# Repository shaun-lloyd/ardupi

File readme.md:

# ArduPi, Ardupilot + Raspberry Pi

ArduPi is an Raspberry Pi hat with sensors and drivers to run ardupilot.

Based entirely on work and with the guidance and lead of [Muhammad Hefny, OBAL](https://github.com/HefnySco/OBAL "Muhammad Hefny, OBAL").

## Thanks

This project stands on the ardupilot & raspberry pi platforms, ardupilot in particular is an outstanding example of open source communities flourishing.

[OBAL, Mohammad Hefny](https://github.com/HefnySco/OBAL "OBAL, Mohammad Hefny"). ArduPi has been created using [OBAL](https://github.com/HefnySco/OBAL "OBAL") as a reference and design inspiration.

ArduPi-v0.1 == OBAL

## Development

Everything in the entire toolchain must be free software. No dependancy on any non-free software is acceptable. With exception of ardupilot:matlab. "I would really love to hear from anyone that can suggest or give advise on how to or the process involved in porting the current control theory to a free software platform, potential financial support is available to any project that can resonable accomplish this task".

The board itself is developed using Kicad v6.0 on both ubuntu and windows.

Linux is the focus however Kicad is available on mac & windows so there is no reason developement couldn't be done any OS and indeed is. As long as anything done on windows is "do-able" on linux then that's cool.

## Solution: ArduPi
The Raspberry pi platform requires some additional hardware to be able to control a vehicle.
The RPI handles ardupilot-cpu / comms:control-telemetry-video, and ardupi handles everything else.

This hardware is designed using OBAL reference.

### Hardware Specification

Raspberry Pi 4b hat.

### IC
- ULN2803:led,buzzer
- ADS1115:current voltage sensor
- IMU9650:IMU
- BMP280:Barometer

### Module
- GPS:ublox module
- ExpressLRS

### Connections
- ?6S 25V input. Bypass circuit for driving motors and BEC with ?5v@6a
- +5V@3A input
- PWM:pca9685
- ESC
- UART
- I2C
- SPI
- Serial
- PWM:servo/esc
- RC:Rx
- Buzzer & Safety Circuit

### Software
TODO

## How you can help :)

Any and all feedback is encouraged.

Anyone with electronics experience can look over our shematics and crtique or even better suggest better circuits or components.

1. QA our schematics/pcb layout.

2. I would like to include ADSB,optical flow,lidar & airspeed sensor. So anyone with expertise and some spare time willing to
share would be really appreciated.

Help documenting and organise schematics such that new users in particular can easily understand and fork.

Suggest better IC's, sensors and features.

Thanks.

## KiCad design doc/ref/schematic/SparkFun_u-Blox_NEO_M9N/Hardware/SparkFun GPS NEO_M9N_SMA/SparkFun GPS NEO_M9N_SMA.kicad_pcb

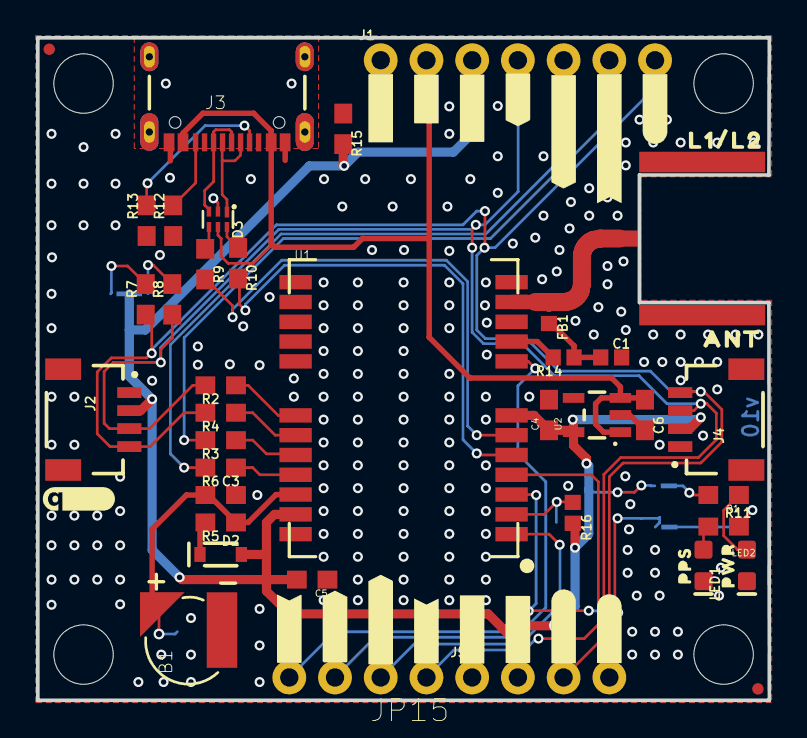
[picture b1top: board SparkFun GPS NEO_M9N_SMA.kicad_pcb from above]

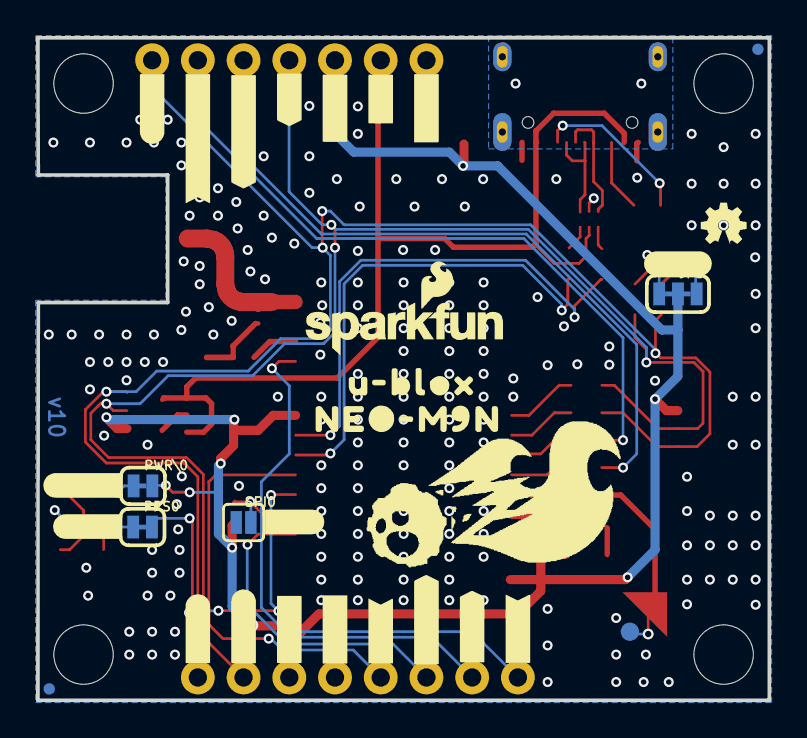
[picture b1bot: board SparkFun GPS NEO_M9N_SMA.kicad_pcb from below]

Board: 2 copper layers, 40.6 x 36.8 mm, 94 parts (31 on the bottom side), 36 nets.

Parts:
B1: 6.8MM_COIN_CELL; ML414H_IV01E
C1: 47pF; 0402
C3, C4, C6: 1.0uF; 0603
C5: 0.1uF; 0603
D2: 0.5A/40V/420mV; SOD-323
D3: PRTR5V0U2F; SOT886
E1: ANTENNA-GROUNDEDEDGE_SMA_SMD; SMA-EDGE-SMD
FB1: FERRITE_BEAD-120_OHM-0402; 0402
FRAME1: FRAME-LETTER; CREATIVE_COMMONS
J1: 1X07_NO_SILK
J2, J4: Qwiic Right Angle; JST04_1MM_RA
J3: USB-C-16P-2LAYER-PADS
J5: 1X04_NO_SILK
JP1, JP31, JP91, JP101: STAND-OFF
JP5: JUMPER-SMT_3_2-NC_TRACE_SILK; SMT-JUMPER_3_2-NC_TRACE_SILK
JP15: 1X04_NO_SILK
JP21, JP61, JP71, JP81: FIDUCIALUFIDUCIAL; MICRO-FIDUCIAL
LED1: BLUE; LED-0603
LED2: RED; LED-0603
LOGO1: OSHW-LOGOMINI; OSHW-LOGO-MINI
LOGO2: SFE_LOGO_NAME_FLAME.1_INCH; SFE_LOGO_NAME_FLAME_.1
PPS0: JUMPER-SMT_2_NC_TRACE_SILK; SMT-JUMPER_2_NC_TRACE_SILK
PWR\0: JUMPER-SMT_2_NC_TRACE_SILK; SMT-JUMPER_2_NC_TRACE_SILK
R1, R5, R11: 1k; 0603
R2, R3, R4, R6: 33; 0603
R7, R8: 2.2k; 0603
R9, R10: 27; 0603
R12, R13: 5.1k; 0603
R14: 33; 0402
R15: 100k; 0603
R16: 10k; 0402
SPI0: JUMPER-SMT_2_NO_SILK; SMT-JUMPER_2_NO_SILK
TP1: TEST-POINT3X4; PAD.03X.04
U1: U-BLOX_NEO-M9N; NEO-M9N_M8T_M8U
U2: 3.3V; SOT23-5
U$1: ##CS##9
U$2: U#BLOX19
U$3: ##SAFE##15
U$4, U$5, U$39, U$40: #3V3#6
U$6, U$42: #5V#1
U$7, U$8, U$38, U$41: #GND#0
U$9: #INT#16
U$10: PPS7
U$11, U$32: #PPS#13
U$12: #SPI#22
U$13: PWR6
U$14: QWIIC_4MM
U$15: #RX#SDI#10
U$16: #SCK#12
U$17: #PWR#1
U$18: #SCL#18
U$19: #SDA#17
U$20: #TX#SDO#11
U$21: NEO_GPS_BOARD_SILK_FINAL#03#JPG
U$22: ##SAFE##11
U$23: L1#L28
U$24: ANT8
U$25: NEO#M9N20
U$26: ##CS##6
U$27: ##RST##12
U$28: ##RST##2
U$29: #I2C#3
U$30: #INT#10
U$31: #PPS#0
U$33: #RX#SDI#4
U$34: #SCK#3
U$35: #SCL#8
U$36: #SDA#9
U$37: #TX#SDO#5

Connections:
3.3V: C4.1, C5.2, D2.A, J1.3, J2.2, J4.2, J5.2, JP5.2, PWR\0.2, R15.2, R16.2, U1.7, U1.23, U2.5
5V: C6.1, D3.5, J1.2, J3.VBUS1, J3.VBUS2, U2.1, U2.3
D+: D3.4, R9.1
D-: D3.6, R10.1
D_SEL: R16.1, SPI0.2, U1.2
GND: B1.-, C1.2, C3.2, C4.2, C5.1, C6.2, D3.2, E1.GND@0, E1.GND@1, J1.1, J2.1, J3.GND, J3.GND2, J4.1, J5.1, LED1.C, LED2.C, R12.1, R13.1, R15.1, SPI0.1, U1.10, U1.12, U1.13, U1.24, U2.2
GPS_ANT1: E1.SIG, FB1.1, U1.11
INT: JP15.1, U1.4
unnamed: PWR\0.1, R1.2
unnamed: LED1.A, R11.1
unnamed: C1.1, FB1.2, R14.1
unnamed: PPS0.1, R11.2
unnamed: JP5.1, R8.2
unnamed: D2.C, R5.2
unnamed: J3.B5, R12.2
unnamed: JP5.3, R7.2
unnamed: J3.A5, R13.2
unnamed: LED2.A, R1.1
unnamed: R9.2, U1.6
unnamed: R10.2, U1.5
PPS: JP15.4, PPS0.2, U1.3
RXI/SDI: J1.5, R6.2
RXLV: R6.1, U1.21
SCL/SCK: J1.7, J2.4, J4.4, J5.4, R4.2, R7.1
SCL_LV: R4.1, U1.19
SDA/~CS: J1.4, J2.3, J4.3, J5.3, R2.2, R8.1
SDA_LV: R2.1, U1.18
SHLD: J3.SHLD1, J3.SHLD2, J3.SHLD3, J3.SHLD4
TXLV: R3.1, U1.20
TXO/SDO: J1.6, R3.2
USB_D+: D3.3, J3.A6, J3.B6
USB_D-: D3.1, J3.A7, J3.B7
VCC_RF: R14.2, U1.9
V_BATT: B1.+, C3.1, R5.1, TP1.P$1, U1.22
~RESET: JP15.3, U1.8
~SAFE: JP15.2, U1.1

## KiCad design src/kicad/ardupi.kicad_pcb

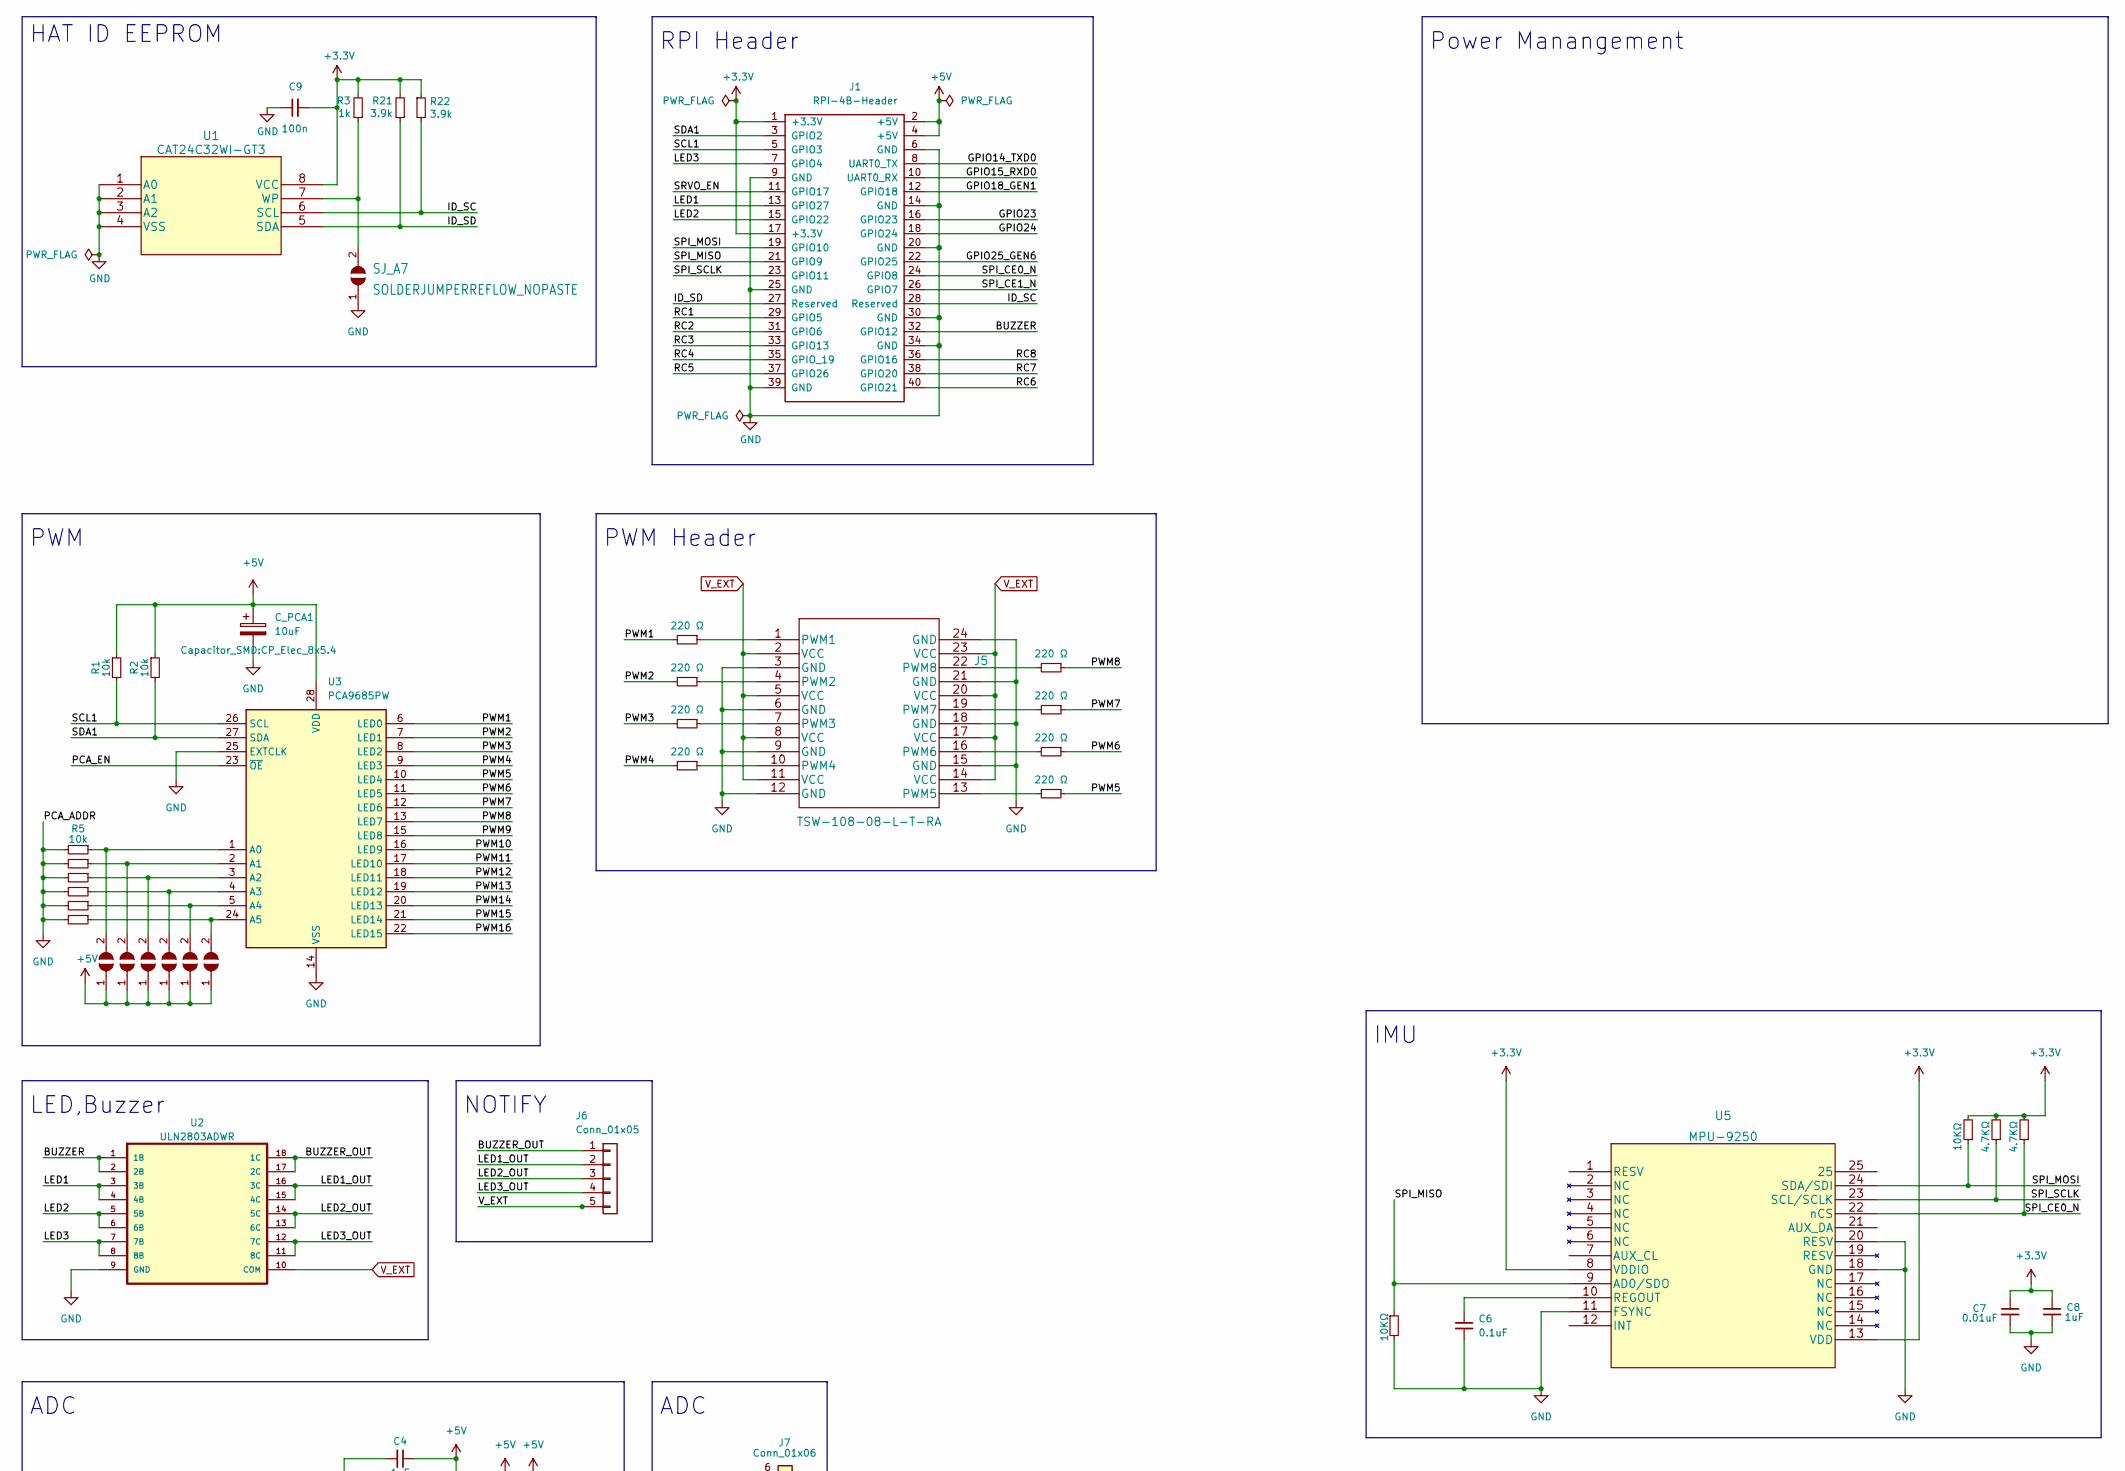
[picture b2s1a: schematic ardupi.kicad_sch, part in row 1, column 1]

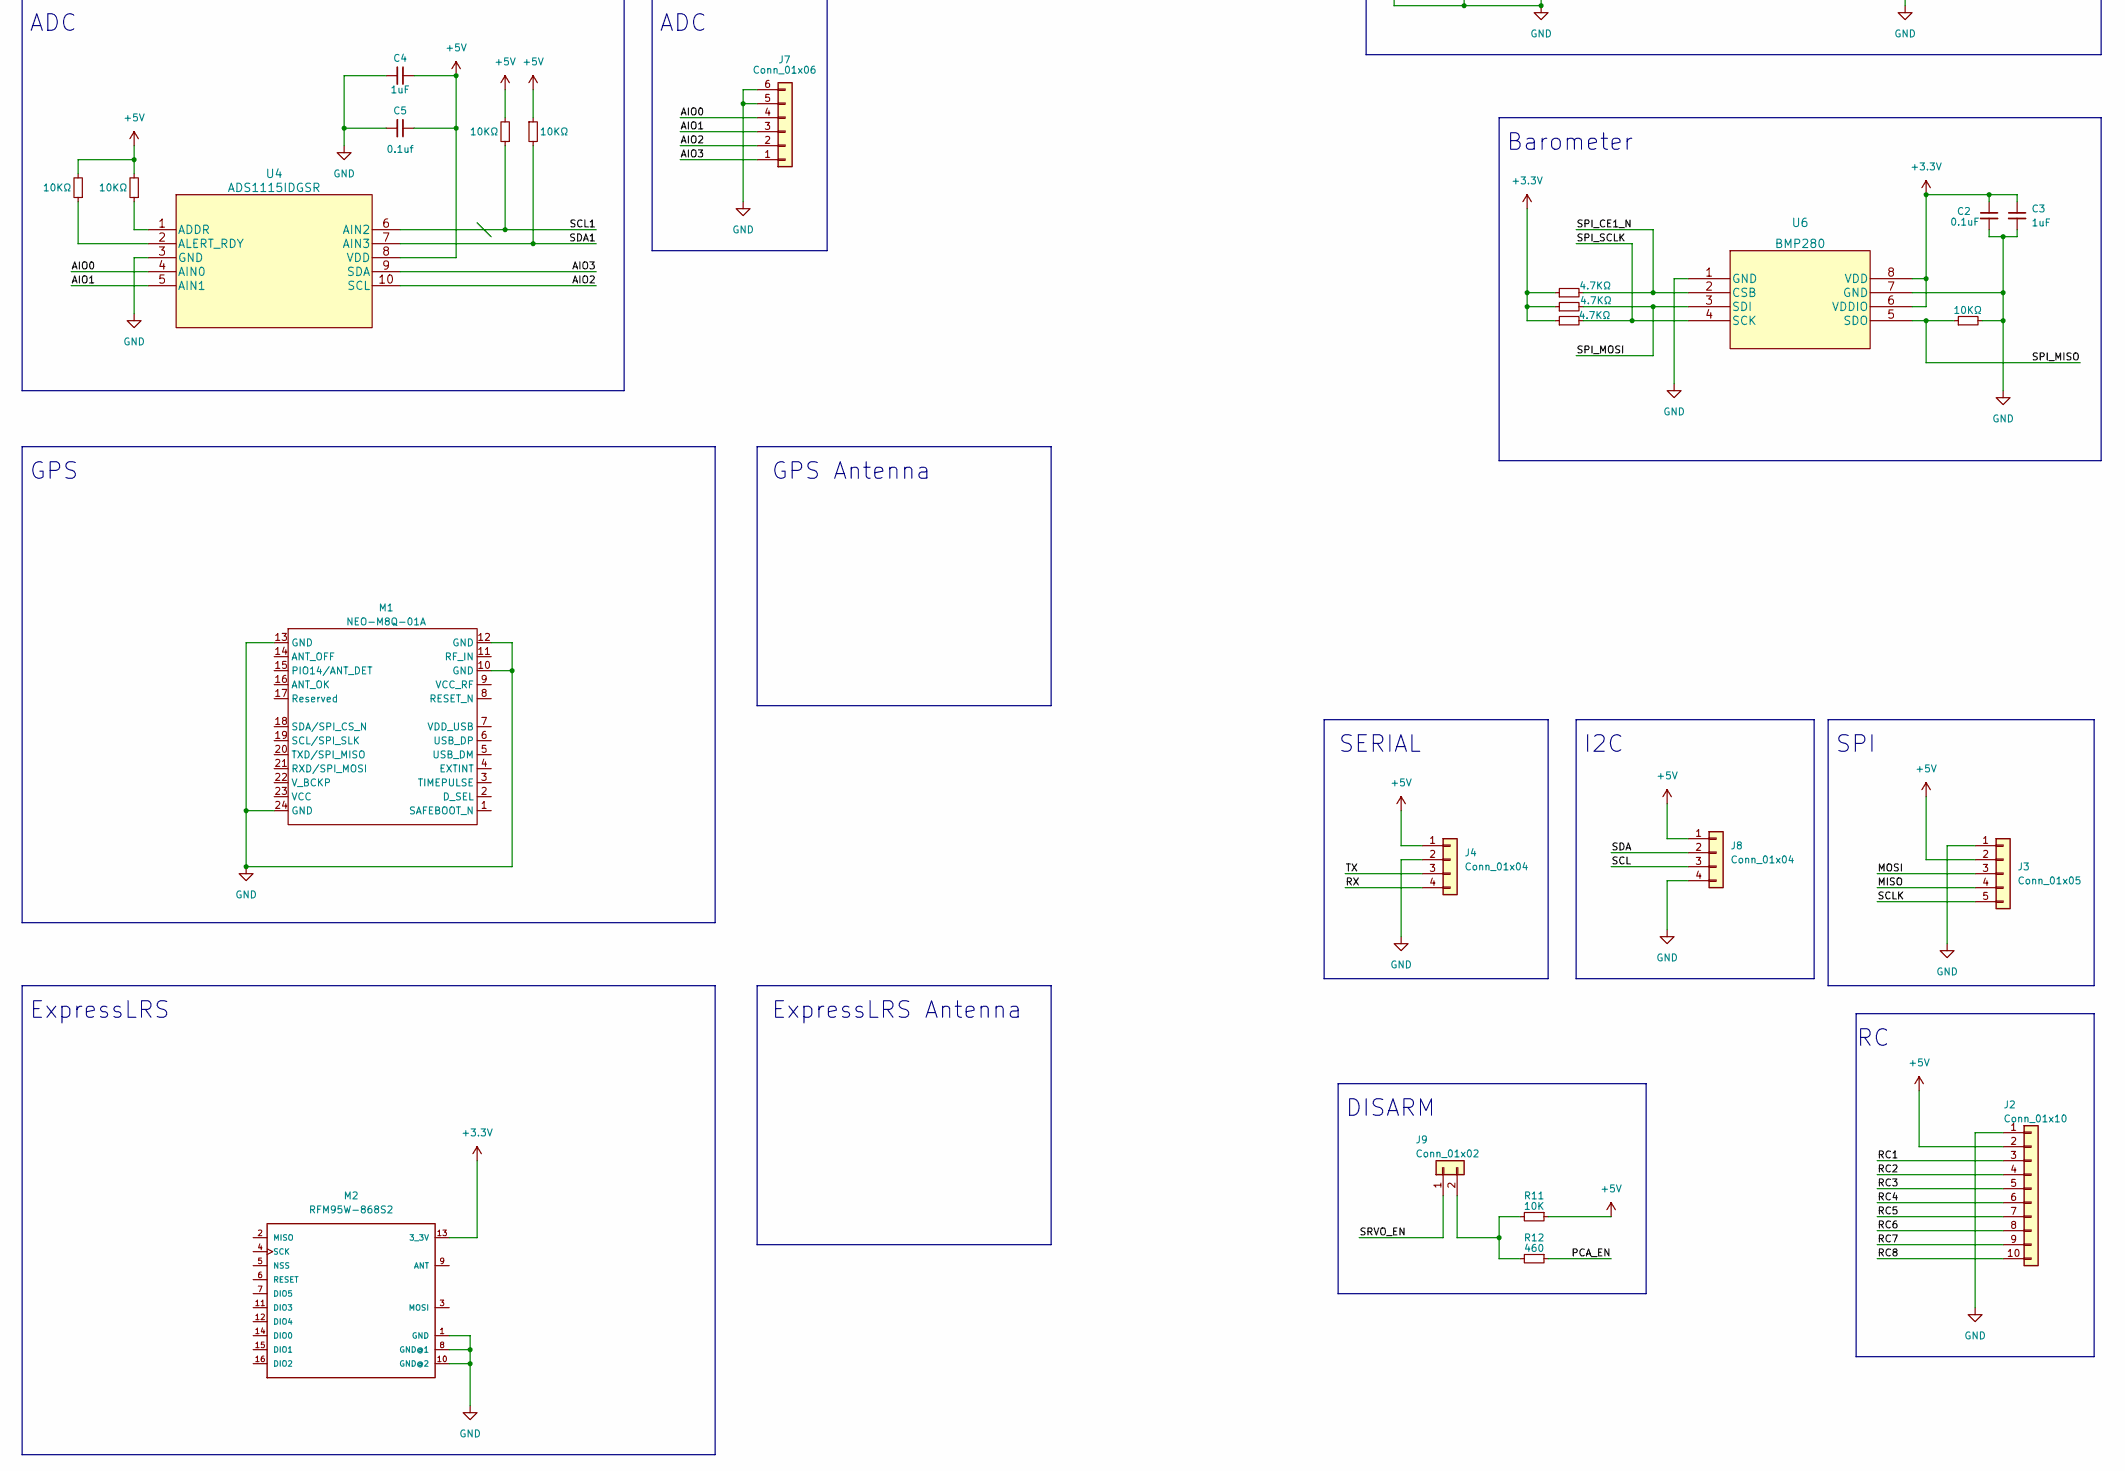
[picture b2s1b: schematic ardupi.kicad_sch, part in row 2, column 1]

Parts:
C2, C6: 0.1uF; C_0402_1005Metric
C3, C4, C8: 1uF; C_0402_1005Metric
C5: 0.1uf; C_0402_1005Metric
C7: 0.01uF; C_0402_1005Metric
C9: 100n; CP_EIA-1608-10_AVX-L
C_PCA1: 10uF; CP_Elec_8x5.4
J1: RPI-4B-Header; PinSocket_2x20_P2.54mm_Vertical
J2: Conn_01x10; JST_EH_B10B-EH-A_1x10_P2.50mm_Vertical
J3, J6: Conn_01x05; JST_EH_B5B-EH-A_1x05_P2.50mm_Vertical
J4, J8: Conn_01x04; JST_EH_B4B-EH-A_1x04_P2.50mm_Vertical
J5: TSW-108-08-L-T-RA; TSW-108-08-T-T-RA_SAI
J7: Conn_01x06; JST_EH_B6B-EH-A_1x06_P2.50mm_Vertical
J9: Conn_01x02; JST_EH_B2B-EH-A_1x02_P2.50mm_Vertical
M1: NEO-M8Q-01A; ublox_NEO
M2: RFM95W-868S2
R1, R2, R5, R9, R10: 10k; R_0402_1005Metric
R3: 1k; R_0402_1005Metric
R6, R7, R8, R11: 10K; R_0402_1005Metric
R12: 460; R_0402_1005Metric
R13, R14, R15, R16, R17, R18, R19, R20: 220 Ω; R_0402_1005Metric
R21, R22: 3.9k; R_0402_1005Metric
R25, R26, R27, R28, R31, R32, R36: 10KΩ; R_0402_1005Metric
R29, R30, R33, R34, R35: 4.7KΩ; R_0402_1005Metric
SJ_A1, SJ_A2, SJ_A3, SJ_A4, SJ_A5, SJ_A6, SJ_A7: SOLDERJUMPERREFLOW_NOPASTE; SOLDERJUMPER_REFLOW_NOPASTE
U1: CAT24C32WI-GT3
U2: ULN2803ADWR
U3: PCA9685PW; PCA9685PW_118
U4: ADS1115IDGSR
U5: MPU-9250; mpu9250
U6: BMP280; bmp280

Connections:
+3V3: C2.1, C3.1, C7.1, C8.1, C9.2, J1.1 (+3.3V), J1.17 (+3.3V), R3.2, R21.2, R22.1, R28.2, R29.2, R30.2, R33.1, R34.1, R35.1, U1.8 (VCC), U5.8 (VDDIO), U5.13 (VDD), U6.6 (VDDIO), U6.8 (VDD); also elsewhere on the board
+5V: C4.1, C5.1, C_PCA1.1, J1.2 (+5V), J1.4 (+5V), J2.2, J3.2, J4.1, J8.1, R1.1, R2.1, R11.1, R25.2, R27.2, R31.2, R32.1, SJ_A1.1, SJ_A2.1, SJ_A3.1, SJ_A4.1, SJ_A5.1, SJ_A6.1, U3.28 (VDD), U4.8 (VDD)
/AIO0: J7.4, U4.4 (AIN0)
/AIO1: J7.3, U4.5 (AIN1)
/AIO2: J7.2, U4.10 (SCL)
/AIO3: J7.1, U4.9 (SDA)
/BUZZER: J1.32 (GPIO12), U2.1 (1B), U2.2 (2B)
/BUZZER_OUT: J6.1, U2.17 (2C), U2.18 (1C)
/GPIO14_TXD0: J1.8 (UART0_TX)
/GPIO15_RXD0: J1.10 (UART0_RX)
/GPIO18_GEN1: J1.12 (GPIO18)
/GPIO23: J1.16 (GPIO23)
/GPIO24: J1.18 (GPIO24)
/GPIO25_GEN6: J1.22 (GPIO25)
/ID_SC: J1.28 (Reserved), R22.2, U1.6 (SCL)
/ID_SD: J1.27 (Reserved), R21.1, U1.5 (SDA)
/LED1: J1.13 (GPIO27), U2.3 (3B), U2.4 (4B)
/LED1_OUT: J6.2, U2.15 (4C), U2.16 (3C)
/LED2: J1.15 (GPIO22), U2.5 (5B), U2.6 (6B)
/LED2_OUT: J6.3, U2.13 (6C), U2.14 (5C)
/LED3: J1.7 (GPIO4), U2.7 (7B), U2.8 (8B)
/LED3_OUT: J6.4, U2.11 (8C), U2.12 (7C)
/MISO: J3.4
/MOSI: J3.3
/PCA_EN: R12.1, U3.23 (~OE)
/PWM1: R13.2, U3.6 (LED0)
/PWM2: R14.2, U3.7 (LED1)
/PWM3: R15.2, U3.8 (LED2)
/PWM4: R16.2, U3.9 (LED3)
/PWM5: R20.1, U3.10 (LED4)
/PWM6: R19.1, U3.11 (LED5)
/PWM7: R18.1, U3.12 (LED6)
/PWM8: R17.1, U3.13 (LED7)
/PWM9: U3.15 (LED8)
/PWM10: U3.16 (LED9)
/PWM11: U3.17 (LED10)
/PWM12: U3.18 (LED11)
/PWM13: U3.19 (LED12)
/PWM14: U3.20 (LED13)
/PWM15: U3.21 (LED14)
/PWM16: U3.22 (LED15)
/RC1: J1.29 (GPIO5), J2.3
/RC2: J1.31 (GPIO6), J2.4
/RC3: J1.33 (GPIO13), J2.5
/RC4: J1.35 (GPIO_19), J2.6
/RC5: J1.37 (GPIO26), J2.7
/RC6: J1.40 (GPIO21), J2.8
/RC7: J1.38 (GPIO20), J2.9
/RC8: J1.36 (GPIO16), J2.10
/RX: J4.4
/SCL: J8.3
/SCL1: J1.5 (GPIO3), R1.2, R31.1, U3.26 (SCL), U4.6 (AIN2)
/SCLK: J3.5
/SDA: J8.2
/SDA1: J1.3 (GPIO2), R2.2, R32.2, U3.27 (SDA), U4.7 (AIN3)
/SPI_CE0_N: J1.24 (GPIO8), R30.1, U5.22 (nCS)
/SPI_CE1_N: J1.26 (GPIO7), R33.2, U6.2 (CSB)
/SPI_MISO: J1.21 (GPIO9), R26.1, R36.1, U5.9 (AD0/SDO), U6.5 (SDO)
/SPI_MOSI: J1.19 (GPIO10), R28.1, R34.2, U5.24 (SDA/SDI), U6.3 (SDI)
/SPI_SCLK: J1.23 (GPIO11), R29.1, R35.2, U5.23 (SCL/SCLK), U6.4 (SCK)
/SRVO_EN: J1.11 (GPIO17), J9.1
/TX: J4.3
GND: C2.2, C3.2, C4.2, C5.2, C6.2, C7.2, C8.2, C9.1, C_PCA1.2, J1.6 (GND), J1.9 (GND), J1.14 (GND), J1.20 (GND), J1.25 (GND), J1.30 (GND), J1.34 (GND), J1.39 (GND), J2.1, J3.1, J4.2, J5.3 (GND), J5.6 (GND), J5.9 (GND), J5.12 (GND), J5.15 (GND), J5.18 (GND), J5.21 (GND), J5.24 (GND), J7.5, J7.6, J8.4, M1.10 (GND), M1.12 (GND), M1.13 (GND), M1.24 (GND), R5.2, R6.2, R7.2, R8.2, R9.2, R10.2, R26.2, R36.2, SJ_A7.1, U1.1 (A0), U1.2 (A1), U1.3 (A2), U1.4 (VSS), U2.9 (GND), U3.14 (VSS), U3.25 (EXTCLK), U4.3 (GND), U5.11 (FSYNC), U5.18 (GND), U5.20 (RESV), U6.1 (GND), U6.7 (GND); also elsewhere on the board
unnamed: C6.1, U5.10 (REGOUT)
unnamed: J5.1 (PWM1), R13.1
unnamed: J5.4 (PWM2), R14.1
unnamed: J5.7 (PWM3), R15.1
unnamed: J5.10 (PWM4), R16.1
unnamed: J5.13 (PWM5), R20.2
unnamed: J5.16 (PWM6), R19.2
unnamed: J5.19 (PWM7), R18.2
unnamed: J5.22 (PWM8), R17.2
unnamed: J9.2, R11.2, R12.2
unnamed: M2.1 (GND), M2.8 (GND@1), M2.10 (GND@2)
unnamed: R3.1, SJ_A7.2, U1.7 (WP)
unnamed: R5.1, SJ_A1.2, U3.1 (A0)
unnamed: R6.1, SJ_A2.2, U3.2 (A1)
unnamed: R7.1, SJ_A3.2, U3.3 (A2)
unnamed: R8.1, SJ_A4.2, U3.4 (A3)
unnamed: R9.1, SJ_A5.2, U3.5 (A4)
unnamed: R10.1, SJ_A6.2, U3.24 (A5)
unnamed: R25.1, U4.2 (ALERT_RDY)
unnamed: R27.1, U4.1 (ADDR)
V_EXT: J5.2 (VCC), J5.5 (VCC), J5.8 (VCC), J5.11 (VCC), J5.14 (VCC), J5.17 (VCC), J5.20 (VCC), J5.23 (VCC), J6.5, U2.10 (COM)

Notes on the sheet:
Barometer
PWM Header
ExpressLRS
IMU
SERIAL
ExpressLRS Antenna
ADC
ADC
SPI
RPI Header
LED,Buzzer
PWM
DISARM
Power Manangement
NOTIFY
GPS Antenna
HAT ID EEPROM
GPS
I2C

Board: 2 copper layers, 69 parts (1 on the bottom side), 54 nets, no tracks yet.

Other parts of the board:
MH1, MH2, MH3, MH4: MountingHole_2.7mm_M2.5
U7: RFM95W-868S2

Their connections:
+3V3: U7.13 (3_3V); also elsewhere on the board
GND: U7.1 (GND), U7.8 (GND@1), U7.10 (GND@2); also elsewhere on the board

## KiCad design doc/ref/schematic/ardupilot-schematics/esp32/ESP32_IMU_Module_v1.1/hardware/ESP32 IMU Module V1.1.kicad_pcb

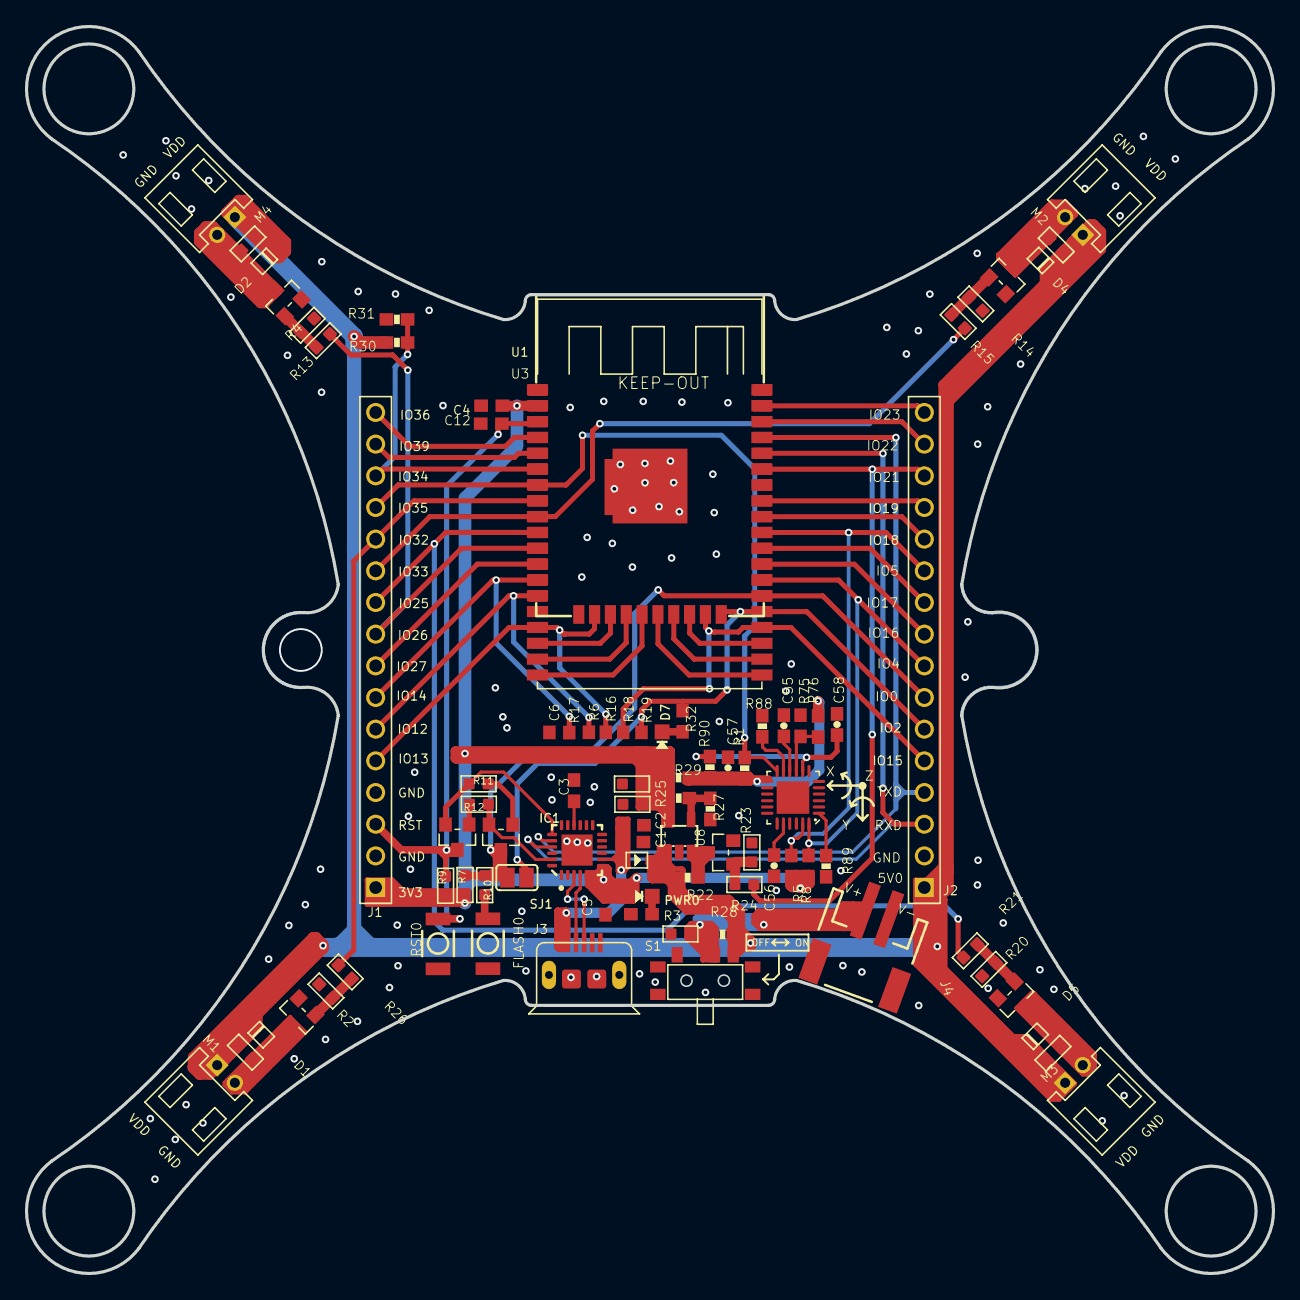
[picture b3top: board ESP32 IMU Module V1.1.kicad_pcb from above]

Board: 2 copper layers, 100.0 x 100.0 mm, 87 parts (1 on the bottom side), 67 nets.

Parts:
C1, C5: 10uF; 0603-NO
C2: 100nF; 0603-NO
C3: 4.7uF; 0603-NO
C4: 10u; C0603
C6: 10uf; 0603-NO
C8, C9, C10, C11, C13: 0.1uF; 0603
C12: 100nf; 0603-NO
C14: 10uF; 0603
C15: 1uF; 0603
C55, C57: 0.1uF; 0603-CAP
C56: 2.2nF; 0603-CAP
C58: 10nF; 0603-CAP
D1, D2, D4, D5: SOD-323F
D6: SS14; SOD323
D7: GREEN; CHIPLED_0805_NOOUTLINE
FLASH0: BUTTON; 157SW
IC1: CP2104; QFN24_4MM_SMSC
J1, J2: HEADER-1X16P-2.54; DIP-1X16-2.54MM
J3: USB-MICRO-5P; MICRO-USB-5P
J4: JST-2-SMD
M1, M2, M3, M4: PH2.0-2P-90-DIP
PWR0: GREEN; CHIPLED_0805_NOOUTLINE
Q1, Q2, Q5, Q6, Q7: AO3400; SOT23@1
Q3, Q4: S8050; SOT23
R1, R22, R88, R89, R90: 10k; 0603-RES
R2, R4, R14, R20, R23: 100k; R0603
R3, R32: 1K; 0603-NO
R5, R8, R75: 4.7K; 0603-NO
R6, R16, R17, R18, R19, R76: NC; 0603-NO
R7, R9, R11, R12: 4.7K; R0603
R10: 470R; R0603
R13, R15, R21, R26: 10k; R0603
R24: NC; R0603
R25, R27: NC; 0603-RES
R28: 0R_NC; 0603-RES
R29: 0R; 0603-RES
R30, R31: 1M; 0603-RES
RST0: BUTTON; 157SW
S1: MSK12C02; SMD7-6.6X2.7X2.5MM
SJ1: SJ
U1: ESP32-WROVER
U3: ESP-WROOM-32
U8: SPX3819; SOT23-5
U25: MPU-6050-1; QFN-24-4MM2
U$1: MAKERFABS_0.3

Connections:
+3V3: C4.1, C5.1, C6.1, C14.2, C15.2, D7.A, IC1.5, IC1.6, IC1.7, J1.1, PWR0.A, R5.1, R6.1, R7.2, R8.1, R9.2, R16.1, R17.1, R18.1, R19.1, R25.1, R29.1, U1.VDD33, U3.2, U8.5
ADO: R75.1, R76.2, U25.9
CLK: U1.CLK, U3.20
CLKIN: R89.2, U25.1
CMD: U1.CMD, U3.19
D+: IC1.3, J3.3
D-: IC1.4, J3.2
DTR: IC1.23, Q3.2, R12.2
FSYNC: R88.2, U25.11
GND: C1.2, C2.2, C3.2, C4.2, C5.2, C6.2, C8.1, C12.2, C14.1, C15.1, C55.2, C56.2, C57.2, C58.2, FLASH0.1, IC1.2, IC1.THERM, J1.2, J1.4, J2.2, J3.5, J3.E1, J3.E2, J3.P1, J3.P2, J4.1, Q1.2, Q2.2, Q5.2, Q6.2, Q7.2, R2.1, R3.1, R4.1, R14.1, R20.1, R23.1, R27.2, R31.2, R75.2, R88.1, R89.1, RST0.1, S1.4, S1.5, S1.6, S1.7, U1.GND, U1.GND2, U1.GND3, U1.GND_2, U3.1, U3.15, U3.38, U3.GND, U8.2, U25.18
IO0: J2.7, Q3.3, R7.1, R10.2, SJ1.2, U1.IO0, U3.25
IO2: J2.6, R19.2, R32.1, SJ1.1, U1.IO2, U3.24
IO4/SDA: J2.8, R8.2, U1.IO4, U3.26, U25.24
IO5/SCL: J2.11, R5.2, U1.IO5, U3.29, U25.23
IO12/MISO: J1.6, R6.2, U1.IO12, U3.14
IO13/MOSI: J1.5, R16.2, U1.IO13, U3.16
IO14/SCLK: J1.7, R17.2, U1.IO14, U3.13
IO15/NSS: J2.5, R18.2, U1.IO15, U3.23
IO16: J2.9, U1.NC1, U3.27
IO17: J2.10, U1.NC2, U3.28
IO18: J2.12, U1.IO18, U3.30
IO19: J2.13, U1.IO19, U3.31
IO21/RES: J2.14, R24.2, U1.IO21, U3.33
IO22/DC: J2.15, U1.IO22, U3.36
IO23: J2.16, U1.IO23, U3.37
IO25: J1.10, R21.2, U1.IO25, U3.10
IO26: J1.9, R13.2, U1.IO26, U3.11
IO27: J1.8, U1.IO27, U3.12
IO32: J1.12, R26.2, U1.IO32, U3.8
IO33: J1.11, R15.2, U1.IO33, U3.9
IO34: J1.14, R30.2, R31.1, U1.IO34, U3.6
IO35: J1.13, R1.1, U1.IO35, U3.7, U25.12
IO36/SVP: J1.16, U1.SENSOR_VP, U3.4
IO39/SVN: J1.15, U1.SENSOR_VN, U3.5
unnamed: C9.1, D1.A, M1.2, Q1.3
unnamed: Q2.1, R4.2, R13.1
unnamed: C10.1, D2.A, M4.2, Q2.3
unnamed: Q1.1, R2.2, R26.1
unnamed: PWR0.C, R3.2
unnamed: Q5.1, R14.2, R15.1
unnamed: C11.1, D4.A, M2.2, Q5.3
unnamed: Q6.1, R20.2, R21.1
unnamed: C13.1, D5.A, M3.2, Q6.3
unnamed: Q7.3, R22.2, U8.3
unnamed: Q7.1, R23.2, R24.1
unnamed: D7.C, R32.2
unnamed: Q4.1, R12.1
unnamed: Q3.1, R11.1
unnamed: FLASH0.2, R10.1
unnamed: R25.2, R27.1, U8.4
unnamed: C56.1, U25.20
unnamed: C55.1, U25.10
NC: U1.NC0, U3.32
RESET: C12.1, J1.3, Q4.3, R9.1, RST0.2, U1.EN, U3.3
RTS: IC1.19, Q4.2, R11.2
RXD: IC1.21, J2.3, U1.RXD0, U3.34
SD0: U1.SD0, U3.21
SD1: U1.SD1, U3.22
SD2: U1.SD2, U3.17
SD3: U1.SD3, U3.18
TXD: IC1.20, J2.4, U1.TXD0, U3.35
VBAT: C8.2, J4.2, R28.2, S1.2
VBUS: C1.1, C2.1, D6.+, IC1.8, J3.1
VBUS1: C3.1, IC1.16
VCC: C57.1, R1.2, R29.2, R76.1, R90.2, U25.13
VDD: C9.2, C10.2, C11.2, C13.2, D1.C, D2.C, D4.C, D5.C, D6.-, J2.1, M1.1, M2.1, M3.1, M4.1, R22.1, R28.1, R30.1, S1.3, U8.1
VIO: C58.1, R90.1, U25.8

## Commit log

2022-05-30 test
2022-05-30 test complete
2022-05-30 typo
2022-05-30 removed kicad backups
2022-05-30 bad wording
2022-05-31 fix Kicad 6.0 format ic's and footprints of components updated
2022-05-31 fix - merge kicad 6.0 updates
2022-05-31 ref OPAL
2022-05-31 add reference schematics
2022-05-31 doc:fix typo and add links
2022-05-31 build: adding git ignore
2022-05-31 elec: PCA9685
2022-05-31 elec: baro & imu
2022-06-01 OBAL reference
2022-06-01 add gitignore/vim swap files
2022-06-01 fixed parts library, +3x4 header for pwm
2022-06-01 parts libary update: PWM 3x4 header should be correct
2022-06-01 + uln2803
2022-06-01 +fix
2022-06-01 +adc
2022-06-01 clean layout
2022-06-01 update status
2022-06-01 +3x8 PWM header
2022-06-01 +parts.md
2022-06-01 elec: ADS1115
2022-06-01 elec: assign GPIOs and correct some pin labels
2022-06-02 +HAT ID EEPROM +standard rpi-4b footprint +clean up of schematic
2022-06-03 - created ardupi parts library. - kicad parts should be completely sorted now, easy to add new parts. - added datasheets for supported ardupilot sensors
2022-06-03 Basic pcb layout
2022-06-04 fix layout
2022-06-04 +todo
2022-06-04 fix todo
2022-06-04 rpi-4b footprint
2022-06-04 replaced pca9685bs back to pca9685PW.
2022-06-05 pca9685bs -> pca9685PW
2022-06-05 version bump
2022-06-05 elec: PCA9685 jumpers
2022-06-06 +ADS1115IDGSR update all symbol footprints VSS = GND
2022-06-06 update symbol definitions, all correct with exception noted in issues
2022-06-06 schematic version bump
2022-06-06 add CAT24C32WI-GT3
2022-06-06 define PWM header pin table.
2022-06-06 +NEO-M8Q-01A module
2022-06-06 + expresslrs.
2022-06-06 elec: 9250 and remove a label between gnd & v
2022-06-06 add IC pinout and pin definition reference
2022-06-06 Set theme jekyll-theme-cayman
2022-06-07 update all symbols & footprints.
2022-06-09 add datasheet ublox stm32
    add reference schematic, ardupilot & gps
2022-06-10 docs
2022-06-13 removed pca9685, fall back to adafruit module. As per original OBAL footprint / design
2022-06-14 +modules, update readme
2022-06-15 + rpi hat specs + neo datasheets + started power management circuit
2022-06-15 version change
2022-06-15 update symbols
2022-06-17 schematic fix and updates
2022-06-17 +xt60 battery input +rpi power pins etc
2022-06-17 update battery connector
2022-06-19 add parts, minor updates
2022-06-20 changed eeprom to UDFN8 package. Need to confirm what pin definition of EPAD.
2022-06-20 EPAD = exposed Pad, connect to gnd
2022-06-22 header modification, add gpio header parts
2022-06-22 update symbols + 3d step files of rpi
2022-06-28 remove GPS/ELRS modules. simplified schematic. update parts add pixhawd standard add ref schematics
2022-06-28 mv datasheet to docs
2022-06-28 bump
2022-07-01 updating netlist and symbol pinouts
2022-07-07 schematic clean up, symbol updates.
    + pixhawk connector standards
2022-07-18 clean up schematic add jst-gh connectors - pixhawk

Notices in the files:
src/hardware/ardupi.kicad_sch:
License: Attribution-ShareAlike 4.0 International (CC BY-SA 4.0)
parts and their libraries:
RELEASED UNDER THE CREATIVE COMMONS ATTRIBUTION SHARE-ALIKE 4.0 LICENSE
HTTPS://CREATIVECOMMONS.ORG/LICENSES/BY-SA/4.0
Copyright 2021 Accelerated Designs. All rights reserved.
